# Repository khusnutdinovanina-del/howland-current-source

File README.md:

# Генератор тока Howland на трёх ОУ

Проект печатной платы в KiCad. Схема генератора тока Howland на трёх
операционных усилителях (корпуса OPA2277, DIP-8).

## Состав проекта

| Что | Где |
|---|---|
| Схема электрическая принципиальная | `howland-current-source.kicad_sch` |
| Печатная плата (2 слоя) | `howland-current-source.kicad_pcb` |
| Библиотека УГО и посадочных мест | сабмодуль `lib` |
| Скрипт проверок и генерации | `run.bat` |
| Результаты (PDF, BOM, Gerber, DRC) | `output/` |

## Как клонировать

Библиотека лежит в отдельном репозитории
[howland-kicad-lib](https://github.com/khusnutdinovanina-del/howland-kicad-lib)
и подключена как git-сабмодуль в папку `lib`. Клонировать нужно так:

```
git clone --recurse-submodules https://github.com/khusnutdinovanina-del/howland-current-source.git
```

Если репозиторий уже склонирован без сабмодуля:

```
git submodule update --init
```

Пути к библиотекам относительные: `${KIPRJMOD}/lib/...`

## Библиотека

В `lib` лежат:
- `howland_gost.kicad_sym`: символ ОУ по ГОСТ 2.759-82;
- `howland_gost_footprints.pretty`: посадочное место `OPA2277_DIP8`.

## Схема

- Рамка и основная надпись по ГОСТ.
- Составной компонент обозначен через точку: DA1.1, DA1.2, DA2.1, DA2.2.
- Классы цепей: `Power` (+12V, -12V, GND), `Signal`, `Default`.
- В полях компонентов заполнено `Manufacturer_Part_Number`.

## Компоненты

Заполни по файлу `output/bom.csv`, чтобы обозначения совпадали со схемой.

| Обозначение | Номинал | Manufacturer_Part_Number |
|---|---|---|
| DA1, DA2 | OPA2277 | OPA2277PA |
| R1, R3, R4, R5, R6, R8 | 10 кОм | RN55D1002FB14 |
| R7 | 125 Ом | RN55D1250FB14 |
| R9 | 9,87 кОм | RN55D9871FB14 |
| J1, J2, J3 | разъём 1x02, шаг 2,54 мм | — |

## Печатная плата

Нормы завода Резонит:
- минимальная ширина дорожки 0,25 мм;
- минимальный зазор 0,25 мм;
- минимальный диаметр сверла 0,3 мм;
- зазор до края платы 0,5 мм.

Дорожки проложены под углом 45°, цепь GND выполнена полигоном
на обоих слоях.

## Проверки и генерация файлов

Запуск: `run.bat`. Скрипт выполняет ERC, DRC, формирует Gerber-файлы,
перечень элементов (BOM) и PDF схемы. Результаты лежат в `output/`.

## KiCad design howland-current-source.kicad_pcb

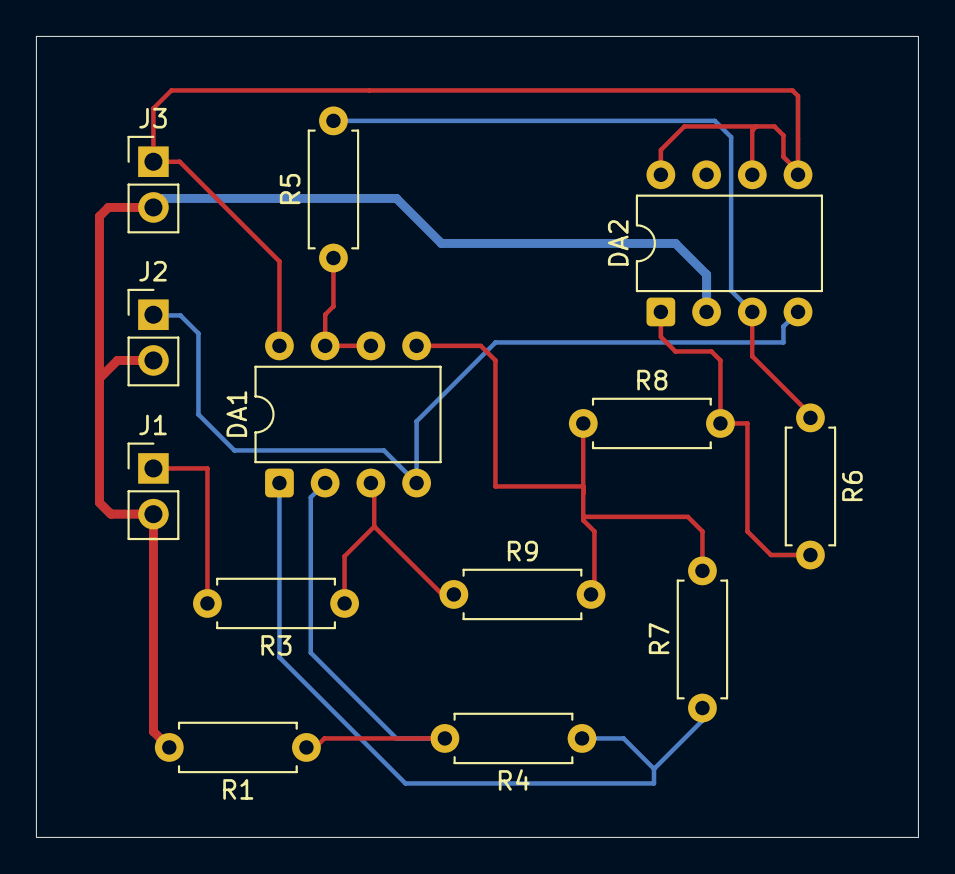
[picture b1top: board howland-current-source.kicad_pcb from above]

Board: 2 copper layers, 49.0 x 44.5 mm, 13 parts (0 on the bottom side), 11 nets.

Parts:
DA1, DA2: DIP-8_W7.62mm
J1, J2, J3: Conn_01x02; PinHeader_1x02_P2.54mm_Vertical
R1, R3, R4, R5, R6, R8: 10k; R_Axial_DIN0207_L6.3mm_D2.5mm_P7.62mm_Horizontal
R7: 125; R_Axial_DIN0207_L6.3mm_D2.5mm_P7.62mm_Horizontal
R9: 9.87k; R_Axial_DIN0207_L6.3mm_D2.5mm_P7.62mm_Horizontal

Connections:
+12V: DA1.8 (V+), DA2.5 (In+), DA2.6 (In-), DA2.8 (V+), J3.1
-12V: DA1.4 (V-), DA2.4 (V-), J2.1
GND: DA2.2 (In-), J1.2, J2.2, J3.2, R1.2
unnamed: DA1.3 (In+), R3.1, R9.1
unnamed: DA1.2 (In-), R1.1, R4.2
unnamed: DA1.1 (Out), R4.1, R7.1
unnamed: DA1.5 (In+), R7.2, R8.1, R9.2
unnamed: DA1.6 (In-), DA1.7 (Out), R5.1
unnamed: DA2.3 (In+), R5.2, R6.1
unnamed: DA2.1 (Out), R6.2, R8.2
unnamed: J1.1, R3.2

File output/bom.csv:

"Refs","Value","Footprint","Qty","DNP"
"DA1","","Package_DIP:DIP-8_W7.62mm","1",""
"DA2","","Package_DIP:DIP-8_W7.62mm","1",""
"J1","Conn_01x02","Connector_PinHeader_2.54mm:PinHeader_1x02_P2.54mm_Vertical","1",""
"R1","10k","Resistor_THT:R_Axial_DIN0207_L6.3mm_D2.5mm_P7.62mm_Horizontal","1",""
"R3","10k","Resistor_THT:R_Axial_DIN0207_L6.3mm_D2.5mm_P7.62mm_Horizontal","1",""
"R4","10k","Resistor_THT:R_Axial_DIN0207_L6.3mm_D2.5mm_P7.62mm_Horizontal","1",""
"R5","10k","Resistor_THT:R_Axial_DIN0207_L6.3mm_D2.5mm_P7.62mm_Horizontal","1",""
"R6","10k","Resistor_THT:R_Axial_DIN0207_L6.3mm_D2.5mm_P7.62mm_Horizontal","1",""
"R7","125","Resistor_THT:R_Axial_DIN0207_L6.3mm_D2.5mm_P7.62mm_Horizontal","1",""
"R8","10k","Resistor_THT:R_Axial_DIN0207_L6.3mm_D2.5mm_P7.62mm_Horizontal","1",""
"R9","9.87k","Resistor_THT:R_Axial_DIN0207_L6.3mm_D2.5mm_P7.62mm_Horizontal","1",""
